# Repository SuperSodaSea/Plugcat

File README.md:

# 🔌Plugcat

- [QSFP-HDMI-OUT-NB7NQ621M v1.1](./QSFP-HDMI-OUT-NB7NQ621M/README.md)

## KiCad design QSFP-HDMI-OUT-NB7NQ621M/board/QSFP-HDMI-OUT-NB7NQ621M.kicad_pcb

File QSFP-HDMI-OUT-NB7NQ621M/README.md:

# QSFP-HDMI-OUT-NB7NQ621M

<p align="center">
    English |
    <a href="./README-zh.md">中文</a>
</p>

---

Bothered by the lack of video output interface on your FPGA boards? This tiny innovative module can help you! QSFP-HDMI-OUT-NB7NQ621M is a QSFP module with HDMI output connector: simply plug it into the QSFP socket on your FPGA boards and get HDMI output capability instantly. This greatly enhances the extensibility of your FPGA boards.

## Features

- Uses [NB7NQ621M](https://www.onsemi.com/products/signal-conditioning-control/redrivers/NB7NQ621M) redriver chip, supports HDMI 2.1 video signal output, bandwidth up to 48Gbps
- HDMI 2.0 TMDS example code provided, supports display modes such as 1920x1080@240Hz, 2560x1440@144Hz, 3840x2160@60Hz, etc.
- HDMI 2.1 FRL example code TBA, you can use arbitrary HDMI 2.1 IP core

## Pin Description

| Name    | Description                                   |
|---------|-----------------------------------------------|
| TX1p    | HDMI CK+                                      |
| TX1n    | HDMI CK-                                      |
| TX2p    | HDMI D0+                                      |
| TX2n    | HDMI D0-                                      |
| TX3p    | HDMI D1+                                      |
| TX3n    | HDMI D1-                                      |
| TX4p    | HDMI D2+                                      |
| TX4n    | HDMI D2-                                      |
| ModPrsL | HDMI cable is plugged in when low             |
| ResetL  | Reset NB7NQ621M when low                      |
| SCL     | I2C clock for both the NB7NQ621M and HDMI DDC |
| SDA     | I2C data for both the NB7NQ621M and HDMI DDC  |

## PCB Information

- Thickness: 1.00mm
- Layer Stackup: JLC04101H-3313

## Verified FPGA Boards

<table>
  <thead>
    <tr>
      <th>FPGA</th>
      <th>Board</th>
      <th>Example</th>
    </tr>
  </thead>
  <tbody>
    <tr>
      <th colspan="3" scope="rowgroup">Xilinx Zynq 7000 SoC</th>
    </tr>
    <tr>
      <td>XC7Z100</td>
      <td>GongZiGe XuanWu ZYNQ7100 + FMC to QSFP daughter board</td>
      <td></td>
    </tr>
    <tr>
      <th colspan="3" scope="rowgroup">Xilinx Kintex Ultrascale</th>
    </tr>
    <tr>
      <td>XCKU060</td>
      <td>Alpha Data ADM-PCIE-KU3</td>
      <td align="center"><a href="./examples/ADM-PCIE-KU3/">🔗</a></td>
    </tr>
    <tr>
      <th colspan="3" scope="rowgroup">Xilinx Virtex Ultrascale</th>
    </tr>
    <tr>
      <td>XCVU095</td>
      <td>BittWare XUS-P3S</td>
      <td></td>
    </tr>
    <tr>
      <th colspan="3" scope="rowgroup">Xilinx Kintex UltraScale+</th>
    </tr>
    <tr>
      <td>XCKU5P</td>
      <td>BoChenJingXin KU5P</td>
      <td align="center"><a href="./examples/BoChenJingXin-KU5P/">🔗</a></td>
    </tr>
    <tr>
      <td>XCKU5P</td>
      <td>RIGUKE RK-XCKU5P-F</td>
      <td align="center"><a href="./examples/RK-XCKU5P-F/">🔗</a></td>
    </tr>
    <tr>
      <td>XCKU5P</td>
      <td>Milianke MLK-H8-CU06-KU5P</td>
      <td align="center"><a href="./examples/MLK-H8-CU06-KU5P/">🔗</a></td>
    </tr>
    <tr>
      <th colspan="3" scope="rowgroup">Xilinx Virtex UltraScale+</th>
    </tr>
    <tr>
      <td>XCVU13P</td>
      <td>Alibaba VU13P</td>
      <td align="center"><a href="./examples/Alibaba-VU13P/">🔗</a></td>
    </tr>
    <tr>
      <th colspan="3" scope="rowgroup">Altera Stratix V GS</th>
    </tr>
    <tr>
      <td>5SGSKF40I3LNAC</td>
      <td>Microsoft Catapult v2 Storey Peak / X930613-001</td>
      <td align="center"><a href="./examples/Storey-Peak/">🔗</a></td>
    </tr>
    <tr>
      <th colspan="3" scope="rowgroup">Altera Arria 10 GX</th>
    </tr>
    <tr>
      <td>10AXF40AA</td>
      <td>Microsoft Catapult v3 Longs Peak / Model: 1768</td>
      <td align="center"><a href="./examples/Longs-Peak/">🔗</a></td>
    </tr>
    <tr>
      <th colspan="3" scope="rowgroup">Altera Stratix 10 GX</th>
    </tr>
    <tr>
      <td>1SG280LN2F43E2VG</td>
      <td>Microsoft A-2020</td>
      <td align="center"><a href="./examples/Microsoft-A-2020/">🔗</a></td>
    </tr>
    <tr>
      <th colspan="3" scope="rowgroup">Pango Titan-2</th>
    </tr>
    <tr>
      <td>PG2T390H</td>
      <td>XiaoYanJing Titan 390H + FMC to QSFP daughter board</td>
      <td></td>
    </tr>
  </tbody>
</table>

## Example Code

The example code can be built on both Windows and Linux.

### Dependencies

- [Python 3](https://www.python.org/) (for build scripts)
- [Java](https://www.java.com/) (for Chisel)
- [Mill](https://mill-build.org/mill/index.html) (for Chisel)
- [Vivado](https://www.amd.com/en/products/software/adaptive-socs-and-fpgas/vivado.html) (for building Xilinx FPGA projects)
- [Quartus Prime](https://www.intel.com/content/www/us/en/products/details/fpga/development-tools/quartus-prime.html) (for building Altera FPGA projects)

### Build Example Code

Execute the following commands in the corresponding directory to build the example code:

```bash
python build.py build
```

The default video mode is 1920x1080@60Hz. To change the video mode, add the following parameters to the build command:

```bash
python build.py build --resolution 2560x1440 --refresh-rate 144
```

Supported video modes:

 - `1920x1080@30/60/120/144/240Hz`
 - `2560x1440@30/60/120/144Hz`
 - `3840x2160@30/60Hz`

Other resolutions can be implemented by modifying the code.

### Programming Bitstream

```bash
python build.py program
```

### Flashing Bitstream

```bash
python build.py flash
```

## Changelog

See [CHANGELOG.md](./CHANGELOG.md).

## Gallery

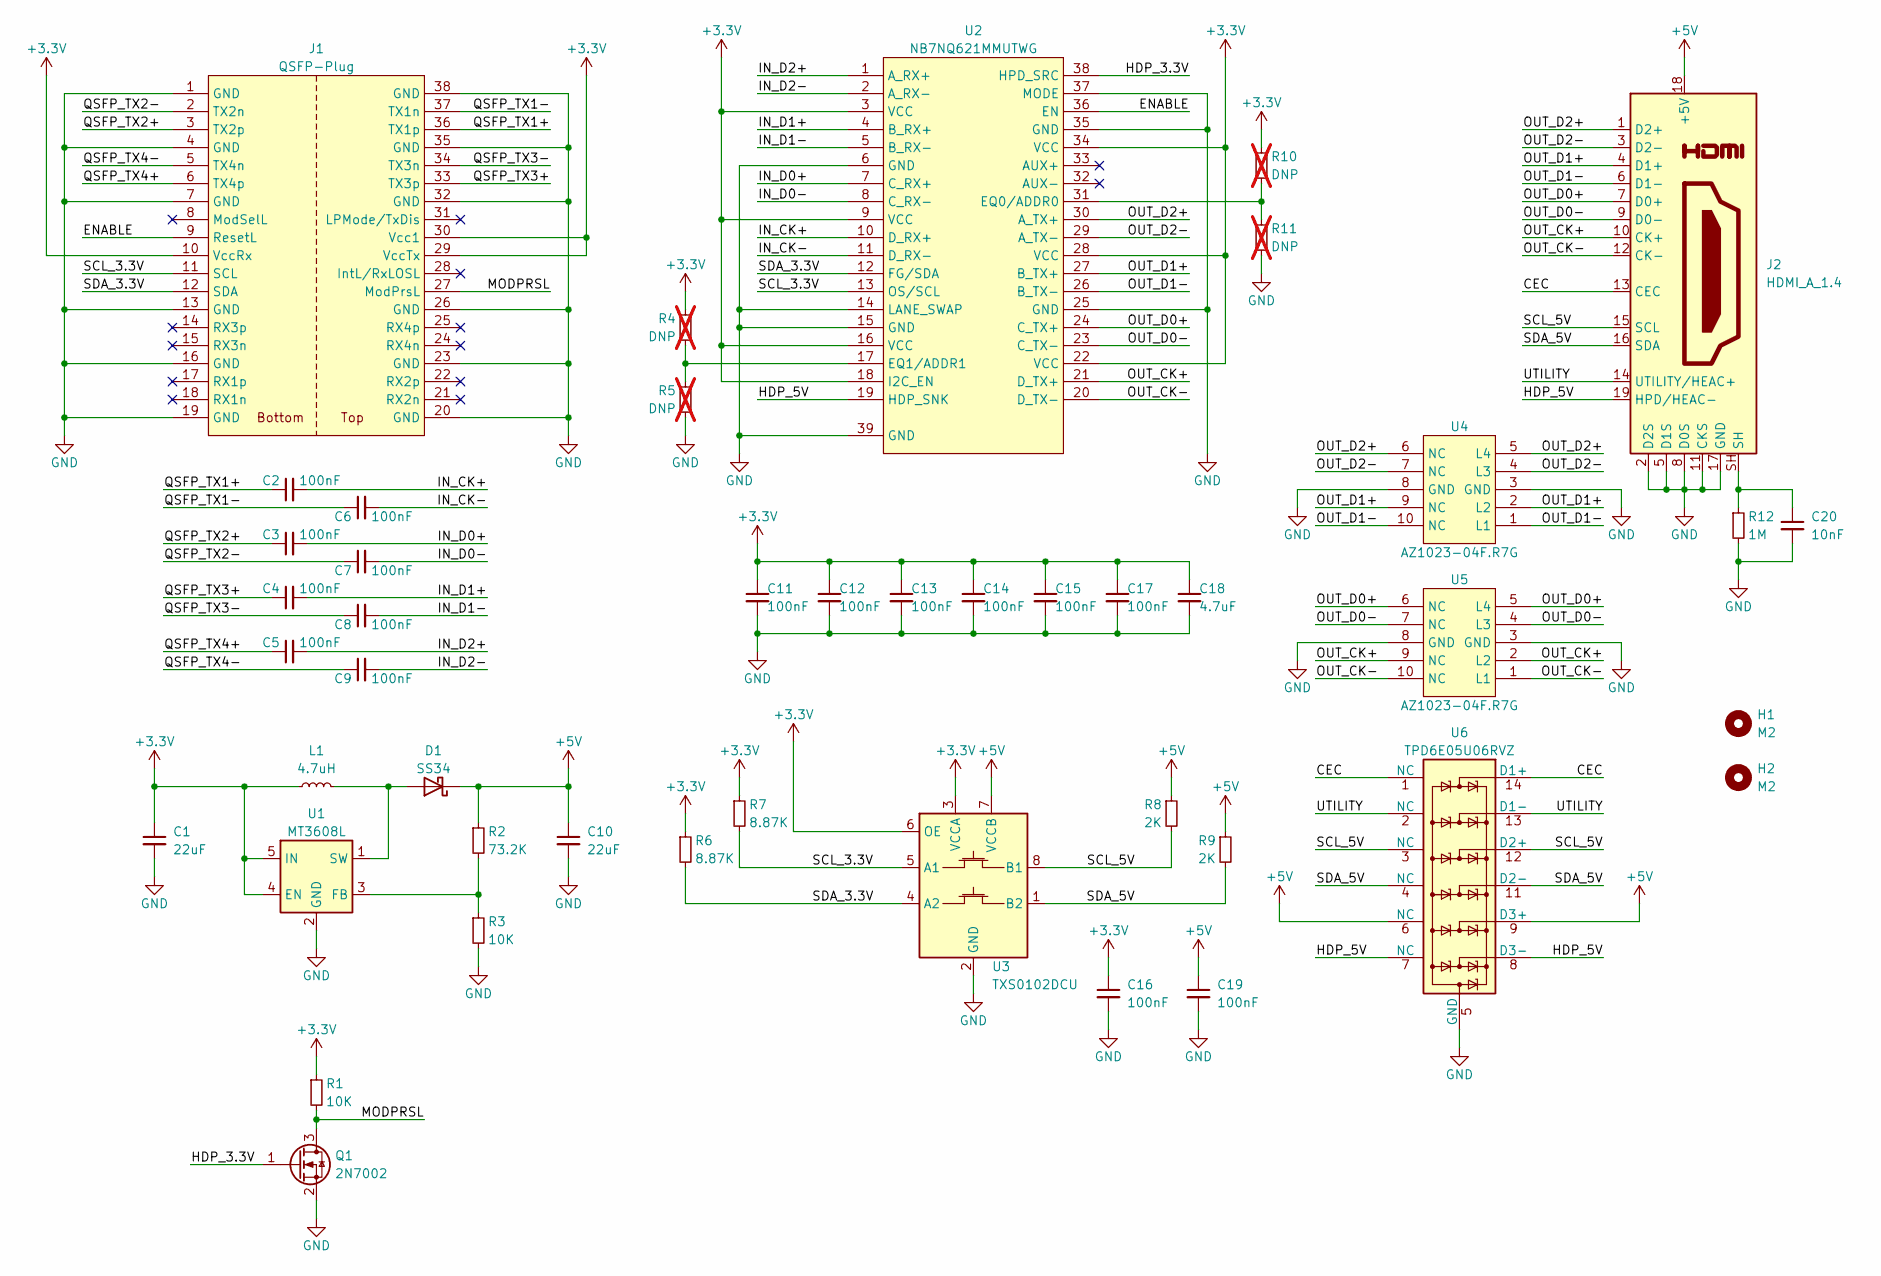
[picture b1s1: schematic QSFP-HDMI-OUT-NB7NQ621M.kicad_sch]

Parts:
C1, C10: 22uF; C_1206_3216Metric_Pad1.33x1.80mm_HandSolder
C2, C3, C4, C5, C6, C7, C8, C9, C11, C12, C13, C14, C15, C16, C17, C19: 100nF; C_0402_1005Metric_Pad0.74x0.62mm_HandSolder
C18: 4.7uF; C_0603_1608Metric_Pad1.08x0.95mm_HandSolder
C20: 10nF; C_1206_3216Metric_Pad1.33x1.80mm_HandSolder
D1: SS34; D_SMA
H1, H2: M2; MountingHole_1.8mm_M1.6
J1: QSFP-Plug
J2: HDMI_A_1.4; HDMI_A_Molex_208658-1001_Horizontal
L1: 4.7uH; L_Sunlord_SWPA3015S
Q1: 2N7002; SOT-23
R1, R3: 10K; R_0603_1608Metric_Pad0.98x0.95mm_HandSolder
R2: 73.2K; R_0603_1608Metric_Pad0.98x0.95mm_HandSolder
R4, R5, R10, R11: DNP; R_0603_1608Metric_Pad0.98x0.95mm_HandSolder; not fitted
R6, R7: 8.87K; R_0603_1608Metric_Pad0.98x0.95mm_HandSolder
R8, R9: 2K; R_0603_1608Metric_Pad0.98x0.95mm_HandSolder
R12: 1M; R_0603_1608Metric_Pad0.98x0.95mm_HandSolder
U1: MT3608L; SOT-23-6
U2: NB7NQ621MMUTWG; Onsemi_X2QFN38_4.05x4.50mm_P0.4mm
U3: TXS0102DCU; VSSOP-8_2.3x2mm_P0.5mm
U4, U5: AZ1023-04F.R7G; Diodes_UDFN-10_1x2.5mm_P0.5mm
U6: TPD6E05U06RVZ; Texas_R-PUSON-N14

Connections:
+3.3V: C1.1, C11.1, C12.1, C13.1, C14.1, C15.1, C16.1, C17.1, C18.1, J1.10 (VccRx), J1.29 (VccTx), J1.30 (Vcc1), L1.1, R1.1, R4.1, R6.1, R7.1, R10.1, U1.4 (EN), U1.5 (IN), U2.3 (VCC), U2.9 (VCC), U2.16 (VCC), U2.18 (I2C_EN), U2.22 (VCC), U2.28 (VCC), U2.34 (VCC), U3.3 (VCCA), U3.6 (OE)
+5V: C10.1, C19.1, D1.1 (K), J2.18 (+5V), R2.1, R8.1, R9.1, U3.7 (VCCB), U6.6 (NC), U6.9 (D3+)
/CEC: J2.13 (CEC), U6.1 (NC), U6.14 (D1+)
/ENABLE: J1.9 (ResetL), U2.36 (EN)
/HDP_3.3V: Q1.1 (G), U2.38 (HPD_SRC)
/HDP_5V: J2.19 (HPD/HEAC-), U2.19 (HDP_SNK), U6.7 (NC), U6.8 (D3-)
/IN_CK+: C2.2, U2.10 (D_RX+)
/IN_CK-: C6.2, U2.11 (D_RX-)
/IN_D0+: C3.2, U2.7 (C_RX+)
/IN_D0-: C7.2, U2.8 (C_RX-)
/IN_D1+: C4.2, U2.4 (B_RX+)
/IN_D1-: C8.2, U2.5 (B_RX-)
/IN_D2+: C5.2, U2.1 (A_RX+)
/IN_D2-: C9.2, U2.2 (A_RX-)
/MODPRSL: J1.27 (ModPrsL), Q1.3 (D), R1.2
/OUT_CK+: J2.10 (CK+), U2.21 (D_TX+), U5.2 (L2), U5.9 (NC)
/OUT_CK-: J2.12 (CK-), U2.20 (D_TX-), U5.1 (L1), U5.10 (NC)
/OUT_D0+: J2.7 (D0+), U2.24 (C_TX+), U5.5 (L4), U5.6 (NC)
/OUT_D0-: J2.9 (D0-), U2.23 (C_TX-), U5.4 (L3), U5.7 (NC)
/OUT_D1+: J2.4 (D1+), U2.27 (B_TX+), U4.2 (L2), U4.9 (NC)
/OUT_D1-: J2.6 (D1-), U2.26 (B_TX-), U4.1 (L1), U4.10 (NC)
/OUT_D2+: J2.1 (D2+), U2.30 (A_TX+), U4.5 (L4), U4.6 (NC)
/OUT_D2-: J2.3 (D2-), U2.29 (A_TX-), U4.4 (L3), U4.7 (NC)
/QSFP_TX1+: C2.1, J1.36 (TX1p)
/QSFP_TX1-: C6.1, J1.37 (TX1n)
/QSFP_TX2+: C3.1, J1.3 (TX2p)
/QSFP_TX2-: C7.1, J1.2 (TX2n)
/QSFP_TX3+: C4.1, J1.33 (TX3p)
/QSFP_TX3-: C8.1, J1.34 (TX3n)
/QSFP_TX4+: C5.1, J1.6 (TX4p)
/QSFP_TX4-: C9.1, J1.5 (TX4n)
/SCL_3.3V: J1.11 (SCL), R7.2, U2.13 (OS/SCL), U3.5 (A1)
/SCL_5V: J2.15 (SCL), R8.2, U3.8 (B1), U6.3 (NC), U6.12 (D2+)
/SDA_3.3V: J1.12 (SDA), R6.2, U2.12 (FG/SDA), U3.4 (A2)
/SDA_5V: J2.16 (SDA), R9.2, U3.1 (B2), U6.4 (NC), U6.11 (D2-)
/UTILITY: J2.14 (UTILITY/HEAC+), U6.2 (NC), U6.13 (D1-)
GND: C1.2, C10.2, C11.2, C12.2, C13.2, C14.2, C15.2, C16.2, C17.2, C18.2, C19.2, C20.2, J1.1 (GND), J1.4 (GND), J1.7 (GND), J1.13 (GND), J1.16 (GND), J1.19 (GND), J1.20 (GND), J1.23 (GND), J1.26 (GND), J1.32 (GND), J1.35 (GND), J1.38 (GND), J2.2 (D2S), J2.5 (D1S), J2.8 (D0S), J2.11 (CKS), J2.17 (GND), Q1.2 (S), R3.2, R5.2, R11.2, R12.2, U1.2 (GND), U2.6 (GND), U2.14 (LANE_SWAP), U2.15 (GND), U2.25 (GND), U2.35 (GND), U2.37 (MODE), U2.39 (GND), U3.2 (GND), U4.3 (GND), U4.8 (GND), U5.3 (GND), U5.8 (GND), U6.5 (GND), U6.10 (GND)
unnamed: C20.1, J2.SH, R12.1
unnamed: D1.2 (A), L1.2, U1.1 (SW)
unnamed: R2.2, R3.1, U1.3 (FB)
unnamed: R10.2, R11.1, U2.31 (EQ0/ADDR0)
unnamed: R4.2, R5.1, U2.17 (EQ1/ADDR1)

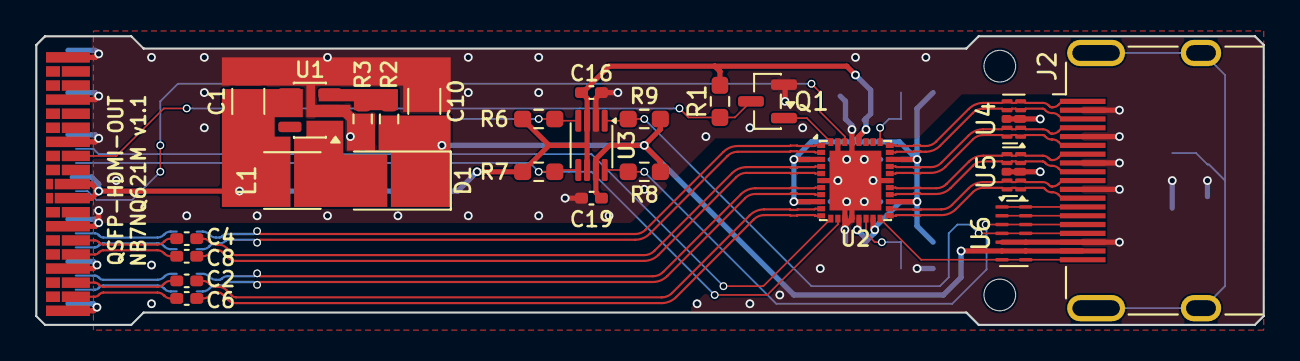
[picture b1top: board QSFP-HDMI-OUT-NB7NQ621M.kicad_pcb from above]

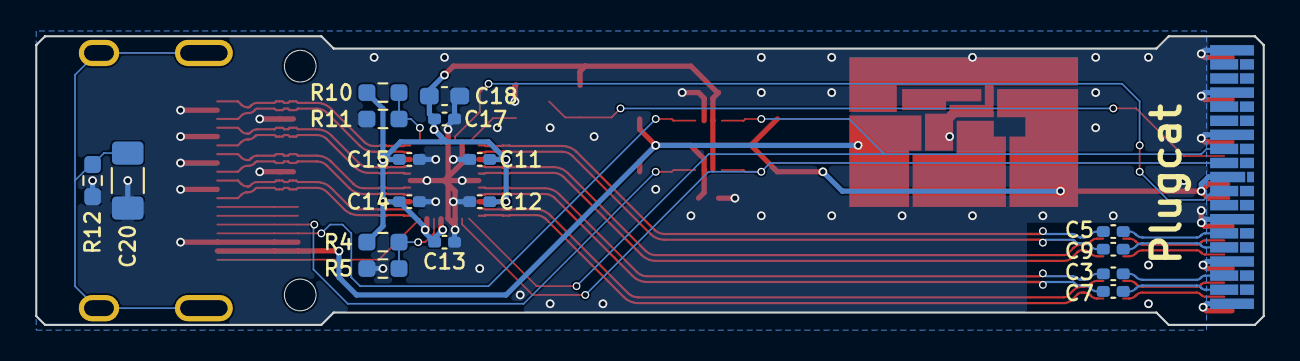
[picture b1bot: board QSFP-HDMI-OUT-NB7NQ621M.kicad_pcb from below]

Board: 4 copper layers, 69.7 x 16.4 mm, 45 parts (17 on the bottom side), 42 nets.

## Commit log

2025-02-16 Resize module photo
2025-02-26 Add HDMI output example code for BoChenJingXinKU5P
2025-02-26 Add HDMI output example code for AlibabaVU13P
2025-02-26 Update HDMI output example
2025-02-27 Update build script
2025-02-27 Fix CreateProject.tcl for AlibabaVU13P
2025-03-01 Update HDMI output example code for AlibabaVU13P
2025-03-02 Rename examples
2025-03-08 Update examples
2025-03-09 Update KiCAD QSFP-Plug symbol
2025-03-13 Bump mill to 0.12.8
2025-03-14 Add timing constraints
2025-03-15 HDMI: Improve timing
2025-03-15 Update timing constraints
2025-03-15 QSFP-HDMI-OUT-NB7NQ621M: Update examples
2025-03-16 I2CMaster: Support read request
2025-03-17 QSFP-HDMI-OUT-NB7NQ621M: Add ADM-PCIE-KU3 example code
2025-03-18 QSFP-HDMI-OUT-NB7NQ621M: Update README
2025-03-25 common: Move /Vivado/sources to /Verilog
2025-03-27 QSFP-HDMI-OUT-NB7NQ621M: Update example code
2025-03-29 Verilog: Improve standard compliance
2025-04-02 HDMIOUTExample: Fix HDMI 2.0 check not working
2025-04-03 QSFP-HDMI-OUT-NB7NQ621M: Improve Verilog standard compliance in examples
2025-04-05 QSFP-HDMI-OUT-NB7NQ621M: Update README Microsoft Catapult v3 Longs Peak verified
2025-04-08 I2CMaster: Add arbitration support
2025-04-09 QSFP-HDMI-OUT-NB7NQ621M: Update README GongZiGe XuanWu ZYNQ7100 verified
2025-04-10 QSFP-HDMI-OUT-NB7NQ621M: Add Storey-Peak example code
2025-04-10 QSFP-HDMI-OUT-NB7NQ621M: Add Longs-Peak example code
2025-04-12 QSFP-HDMI-OUT-NB7NQ621M: Minor update of examples
2025-04-15 QSFP-HDMI-OUT-NB7NQ621M: Update README Add description for Quartus Prime
2025-04-21 QSFP-HDMI-OUT-NB7NQ621M: Update README XiaoYanJing Titan 390H verified
2025-05-17 QSFP-HDMI-OUT-NB7NQ621M: Add RK-XCKU5P-F example code
2025-05-17 QSFP-HDMI-OUT-NB7NQ621M: Update README RK-XCKU5P-F verified
2025-05-28 QSFP-HDMI-OUT-NB7NQ621M: Add MLK-H8-CU06-KU5P example code
2025-05-28 QSFP-HDMI-OUT-NB7NQ621M: Update README MLK-H8-CU06-KU5P verified
2025-05-31 QSFP-HDMI-OUT-NB7NQ621M: Update README Use table in "Verified FPGA Boards" section
2025-06-02 KiCad: Upgrade files to 9.0
2025-06-02 KiCad: Rename KiCAD -> KiCad
2025-09-17 MLK-H8-CU06-KU5P: Update constraints
2025-09-18 Longs-Peak: Fix timing constraints
2025-09-19 Chisel: Upgrade mill to 1.0.5 & chisel to 7.0.0
2025-09-24 QSFP-HDMI-OUT-NB7NQ621M: Update footprints
2025-11-04 QSFP-HDMI-OUT-NB7NQ621M: Update README BittWare XUS-P3S verified
2025-11-10 QSFP-HDMI-OUT-NB7NQ621M: Update to v1.1
2025-11-23 Verilog: Update common example code
2025-11-25 QSFP-HDMI-OUT-NB7NQ621M: Add Microsoft-A-2020 example code
2025-11-26 QSFP-HDMI-OUT-NB7NQ621M: Add changelog
2025-11-29 QSFP-HDMI-OUT-NB7NQ621M: Update module photo
2025-11-29 QSFP-HDMI-OUT-NB7NQ621M: Update changelog
2026-01-16 RK-XCKU5P-F: Use clock_200 instead of clock_50
2026-03-15 RK-XCKU5P-F: Update constraints
2026-05-23 Misc: Update to KiCad 10.0
2026-06-26 KiCad: Use v10 .kicad_symdir format
